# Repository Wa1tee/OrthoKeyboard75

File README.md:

# OrthoKeyboard75

## Features:
 - Keyboard with a split ortholinear layout
    - Two 5x6 clusters of buttons
    - 3.5" touch screen in between
 - USB Type-C connector
 - A form factor that fits in a standard 60% keyboard case
 - On board STM32 microcontroller - No separate controller devboard like Pro Micro
 - Support for MX and Kailh Choc switches
 - Possible support for Kailh X switches
 
## ToDo hardware:
- [x] Switch matrix with diodes
- [x] Choose a 3V3 Regulator
- [x] Choose the STM32F303 version
- [x] Wiring for the rows and columns to the MCU
- [x] Begin laying out the PCB
- [ ] Standoff positions for 60% case
- [ ] Choose TFT module
- [ ] Component layout
- [ ] Routing

## ToDo software:
- [ ] Everything lol :D

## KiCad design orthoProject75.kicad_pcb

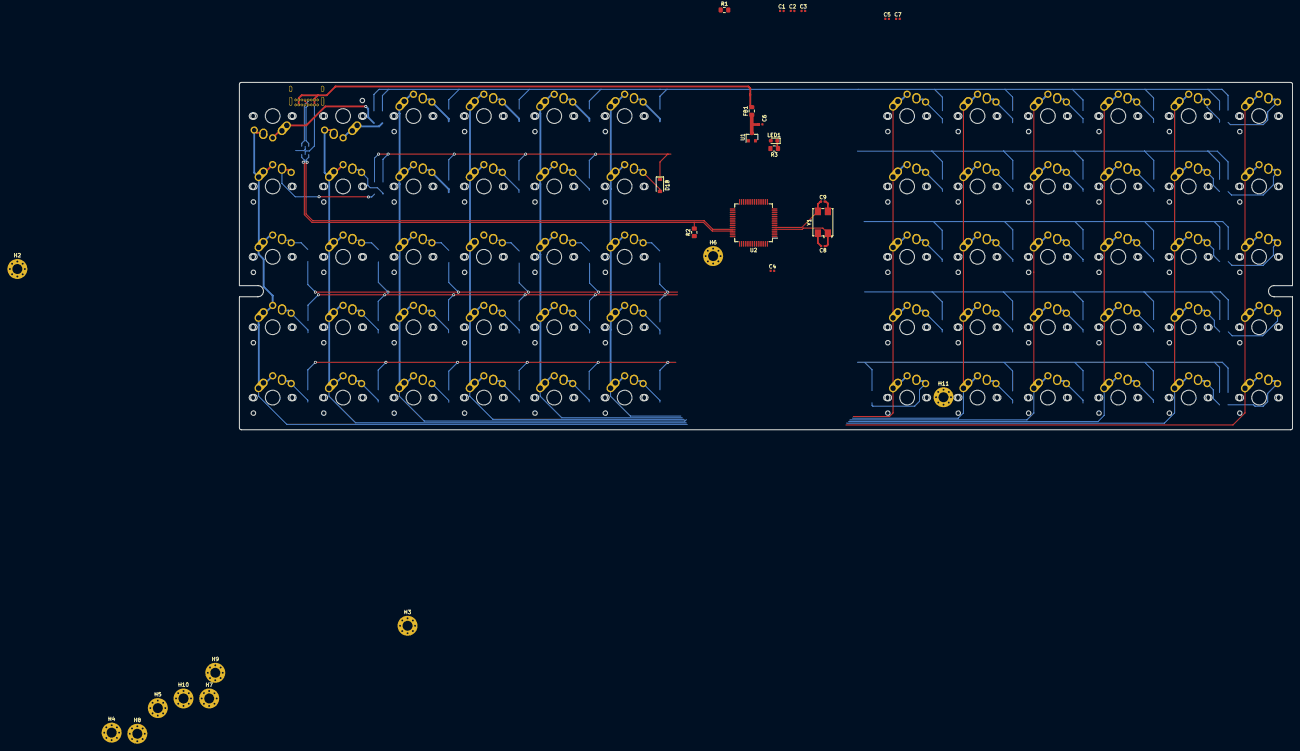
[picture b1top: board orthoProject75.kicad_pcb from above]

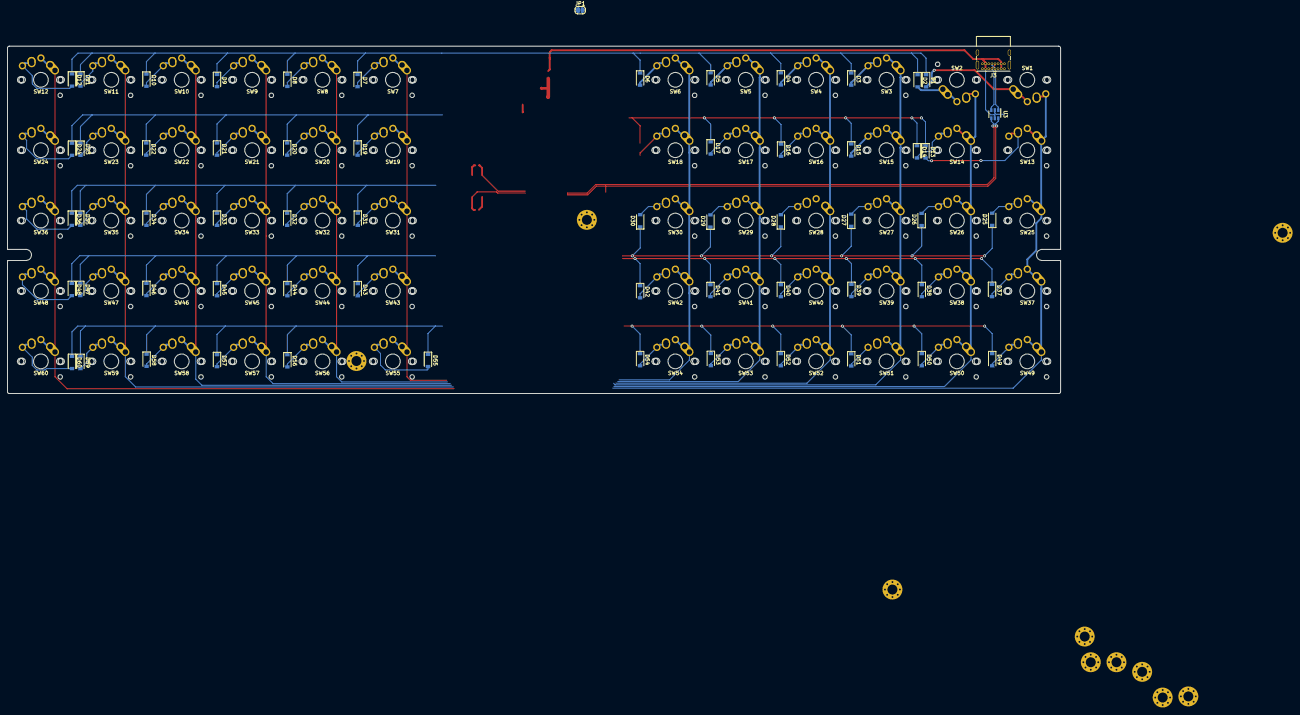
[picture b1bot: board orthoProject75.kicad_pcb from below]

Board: 2 copper layers, 285.0 x 94.0 mm, 150 parts (62 on the bottom side), 89 nets.

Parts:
C1: 4u7; C_0402_1005Metric
C2, C3, C4, C5: 100n; C_0402_1005Metric
C6, C7: 1u; C_0402_1005Metric
C8, C9: 30p; C_0402_1005Metric
D1, D2, D3, D4, D5, D6, D7, D8, D9, D10, D11, D12, D13, D14, D15, D16, D17, D18, D19, D20, D21, D22, D23, D24, D25, D26, D27, D28, D29, D30, D31, D32, D33, D34, D35, D36, D37, D38, D39, D40, D41, D42, D43, D44, D45, D46, D47, D48, D49, D50, D51, D52, D53, D54, D55, D56, D57, D58, D59, D60: D; D_SOD-123
FB1: 100R; L_0805_2012Metric_Pad1.15x1.40mm_HandSolder
H2, H3, H4, H5, H6, H7, H8, H9, H10, H11: MountingHole_Pad; MountingHole_2.7mm_M2.5_Pad_Via
J3: USB_C_Receptacle_USB2.0; USB_C_Receptacle_GCT_USB4085
JP1: SolderJumper_2_Open; SolderJumper-2_P1.3mm_Open_RoundedPad1.0x1.5mm
LED1: LED; LED_0603_1608Metric_Pad1.05x0.95mm_HandSolder
R1, R2, R3: 1k5; R_0805_2012Metric_Pad1.15x1.40mm_HandSolder
SW1, SW2, SW3, SW4, SW5, SW6, SW7, SW8, SW9, SW10, SW11, SW12, SW13, SW14, SW15, SW16, SW17, SW18, SW19, SW20, SW21, SW22, SW23, SW24, SW25, SW26, SW27, SW28, SW29, SW30, SW31, SW32, SW33, SW34, SW35, SW36, SW37, SW38, SW39, SW40, SW41, SW42, SW43, SW44, SW45, SW46, SW47, SW48, SW49, SW50, SW51, SW52, SW53, SW54, SW55, SW56, SW57, SW58, SW59, SW60: SW_Push; MX-Alps-Choc-1U-NoLED
U1: XC6206P332MR; SOT-23
U2: STM32F303RCTx; LQFP-64_10x10mm_P0.5mm
U3: USBLC6-2SC6; SOT-23-6
Y1: 32MHz; Crystal_SMD_7050-4Pin_7.0x5.0mm

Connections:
+3V3: C1.1, C2.1, C3.1, C4.1, C5.1, C7.1, JP1.1, LED1.2, R2.1, U1.2, U2.1, U2.13, U2.19, U2.32, U2.48, U2.64
+5V: FB1.2, J3.A4, J3.A9, J3.B4, J3.B9, U3.5
Col1: SW1.1, SW13.2, SW25.2, SW37.2, SW49.2, U2.56
Col2: SW2.1, SW14.2, SW26.2, SW38.2, SW50.2, U2.57
Col3: SW3.2, SW15.2, SW27.2, SW39.2, SW51.2, U2.58
Col4: SW4.2, SW16.2, SW28.2, SW40.2, SW52.2, U2.59
Col5: SW5.2, SW17.2, SW29.2, SW41.2, SW53.2, U2.61
Col6: SW6.2, SW18.2, SW30.2, SW42.2, SW54.2, U2.62
Col7: SW7.2, SW19.2, SW31.2, SW43.2, SW55.2, U2.36, U2.54
Col8: SW8.2, SW20.2, SW32.2, SW44.2, SW56.2, U2.37
Col9: SW9.2, SW21.2, SW33.2, SW45.2, SW57.2, U2.38
Col10: SW10.2, SW22.2, SW34.2, SW46.2, SW58.2, U2.39
Col11: SW11.2, SW23.2, SW35.2, SW47.2, SW59.2, U2.40
Col12: SW12.2, SW24.2, SW36.2, SW48.2, SW60.2, U2.41
GND: C1.2, C2.2, C3.2, C4.2, C5.2, C6.2, C7.2, C8.2, C9.2, H2.1, H3.1, H4.1, H5.1, H6.1, H7.1, H8.1, H9.1, H10.1, H11.1, J3.A1, J3.A12, J3.B1, J3.B12, R1.2, R3.2, U1.1, U2.12, U2.31, U2.47, U2.63, U3.2, Y1.2, Y1.4
HSE_IN: C8.1, U2.5, Y1.1
HSE_OUT: C9.1, U2.6, Y1.3
unnamed: C6.1, FB1.1, U1.3
unnamed: D1.2, SW1.2
unnamed: D2.2, SW2.2
unnamed: D3.2, SW3.1
unnamed: D4.2, SW4.1
unnamed: D5.2, SW5.1
unnamed: D6.2, SW6.1
unnamed: D7.2, SW7.1
unnamed: D8.2, SW8.1
unnamed: D9.2, SW9.1
unnamed: D10.2, SW10.1
unnamed: D11.2, SW11.1
unnamed: D12.2, SW12.1
unnamed: D13.2, SW13.1
unnamed: D14.2, SW14.1
unnamed: D15.2, SW15.1
unnamed: D16.2, SW16.1
unnamed: D17.2, SW17.1
unnamed: D18.2, SW18.1
unnamed: D19.2, SW19.1
unnamed: D20.2, SW20.1
unnamed: D21.2, SW21.1
unnamed: D22.2, SW22.1
unnamed: D23.2, SW23.1
unnamed: D24.2, SW24.1
unnamed: D25.2, SW25.1
unnamed: D26.2, SW26.1
unnamed: D27.2, SW27.1
unnamed: D28.2, SW28.1
unnamed: D29.2, SW29.1
unnamed: D30.2, SW30.1
unnamed: D31.2, SW31.1
unnamed: D32.2, SW32.1
unnamed: D33.2, SW33.1
unnamed: D34.2, SW34.1
unnamed: D35.2, SW35.1
unnamed: D36.2, SW36.1
unnamed: D37.2, SW37.1
unnamed: D38.2, SW38.1
unnamed: D39.2, SW39.1
unnamed: D40.2, SW40.1
unnamed: D41.2, SW41.1
unnamed: D42.2, SW42.1
unnamed: D43.2, SW43.1
unnamed: D44.2, SW44.1
unnamed: D45.2, SW45.1
unnamed: D46.2, SW46.1
unnamed: D47.2, SW47.1
unnamed: D48.2, SW48.1
unnamed: D49.2, SW49.1
unnamed: D50.2, SW50.1
unnamed: D51.2, SW51.1
unnamed: D52.2, SW52.1
unnamed: D53.2, SW53.1
unnamed: D54.2, SW54.1
unnamed: D55.2, SW55.1
unnamed: D56.2, SW56.1
unnamed: D57.2, SW57.1
unnamed: D58.2, SW58.1
unnamed: D59.2, SW59.1
unnamed: D60.2, SW60.1
unnamed: JP1.2, R1.1, U2.60
unnamed: LED1.1, R3.1
Row1: D1.1, D2.1, D3.1, D4.1, D5.1, D6.1, D7.1, D8.1, D9.1, D10.1, D11.1, D12.1, U2.9
Row2: D13.1, D14.1, D15.1, D16.1, D17.1, D18.1, D19.1, D20.1, D21.1, D22.1, D23.1, D24.1, U2.10
Row3: D25.1, D26.1, D27.1, D28.1, D29.1, D30.1, D31.1, D32.1, D33.1, D34.1, D35.1, D36.1, U2.11
Row4: D37.1, D38.1, D39.1, D40.1, D41.1, D42.1, D43.1, D44.1, D45.1, D46.1, D47.1, D48.1, U2.14
Row5: D49.1, D50.1, D51.1, D52.1, D53.1, D54.1, D55.1, D56.1, D57.1, D58.1, D59.1, D60.1
USBD+: R2.2, U2.45, U3.6
USBD-: U2.44, U3.4
USB_D+: J3.A6, J3.B6, U3.1
USB_D-: J3.A7, J3.B7, U3.3

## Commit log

2020-02-01 Initial commit of the project files
2020-02-01 Added features title to readme
2021-03-02 Created PCB layout. Routed: Switch matrix & diodes, USB, Power
2021-03-02 Added 5k1 resistors to type-c CC pins
2021-03-02 Added keyboard matrix
2021-03-02 Added plate graphic
2021-03-02 Added files
